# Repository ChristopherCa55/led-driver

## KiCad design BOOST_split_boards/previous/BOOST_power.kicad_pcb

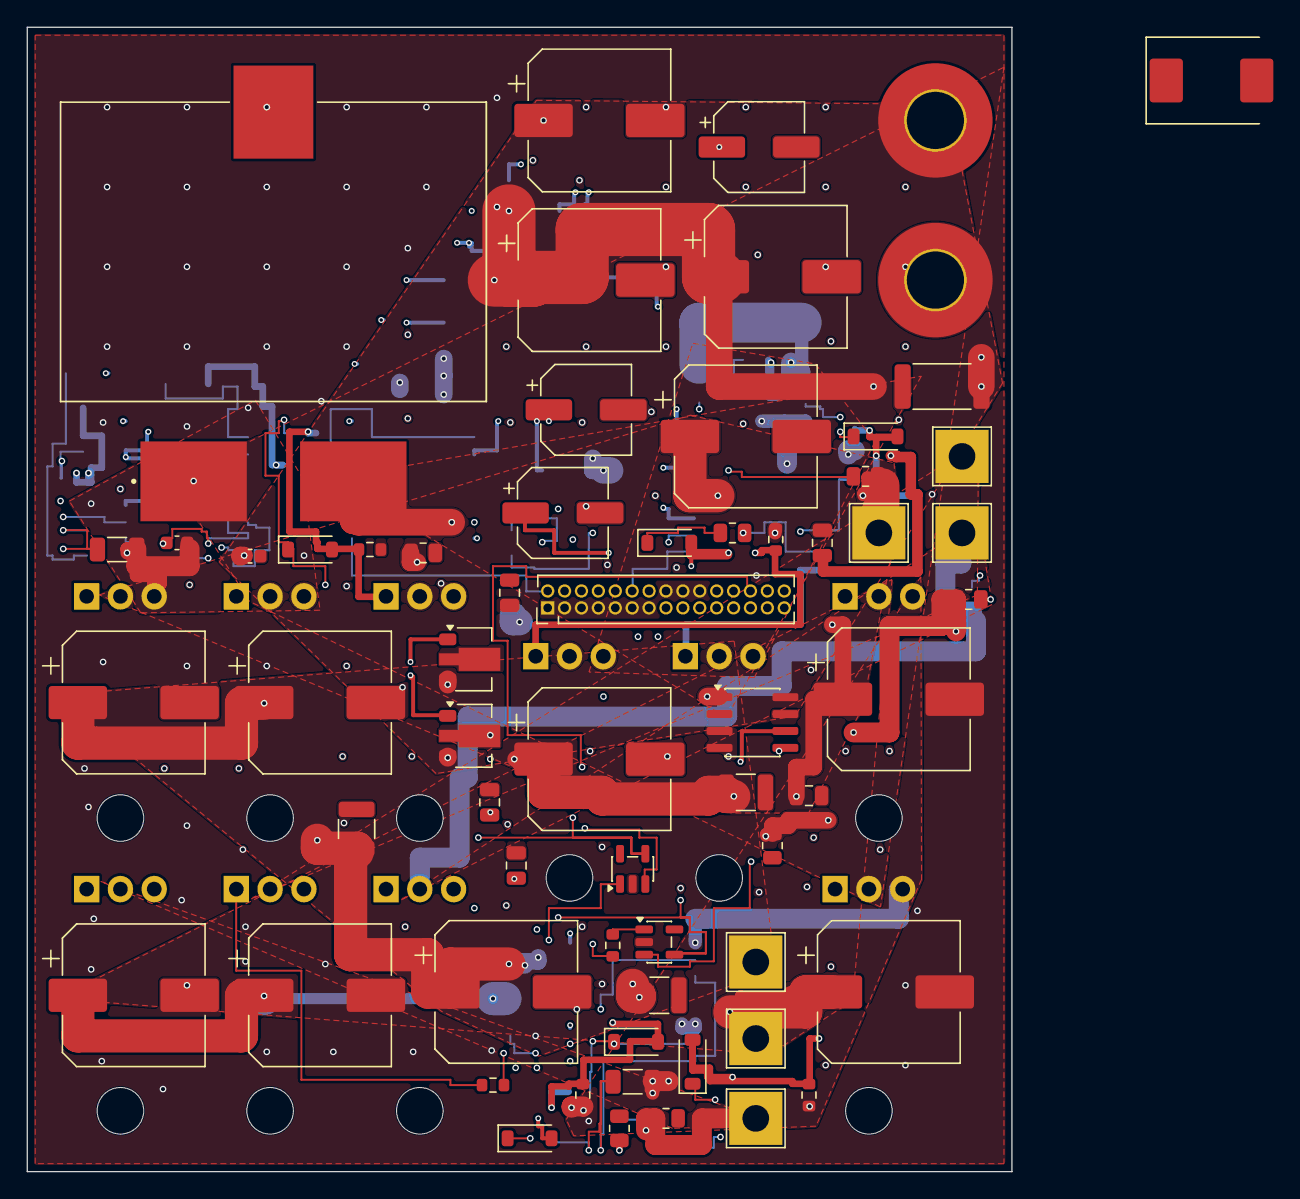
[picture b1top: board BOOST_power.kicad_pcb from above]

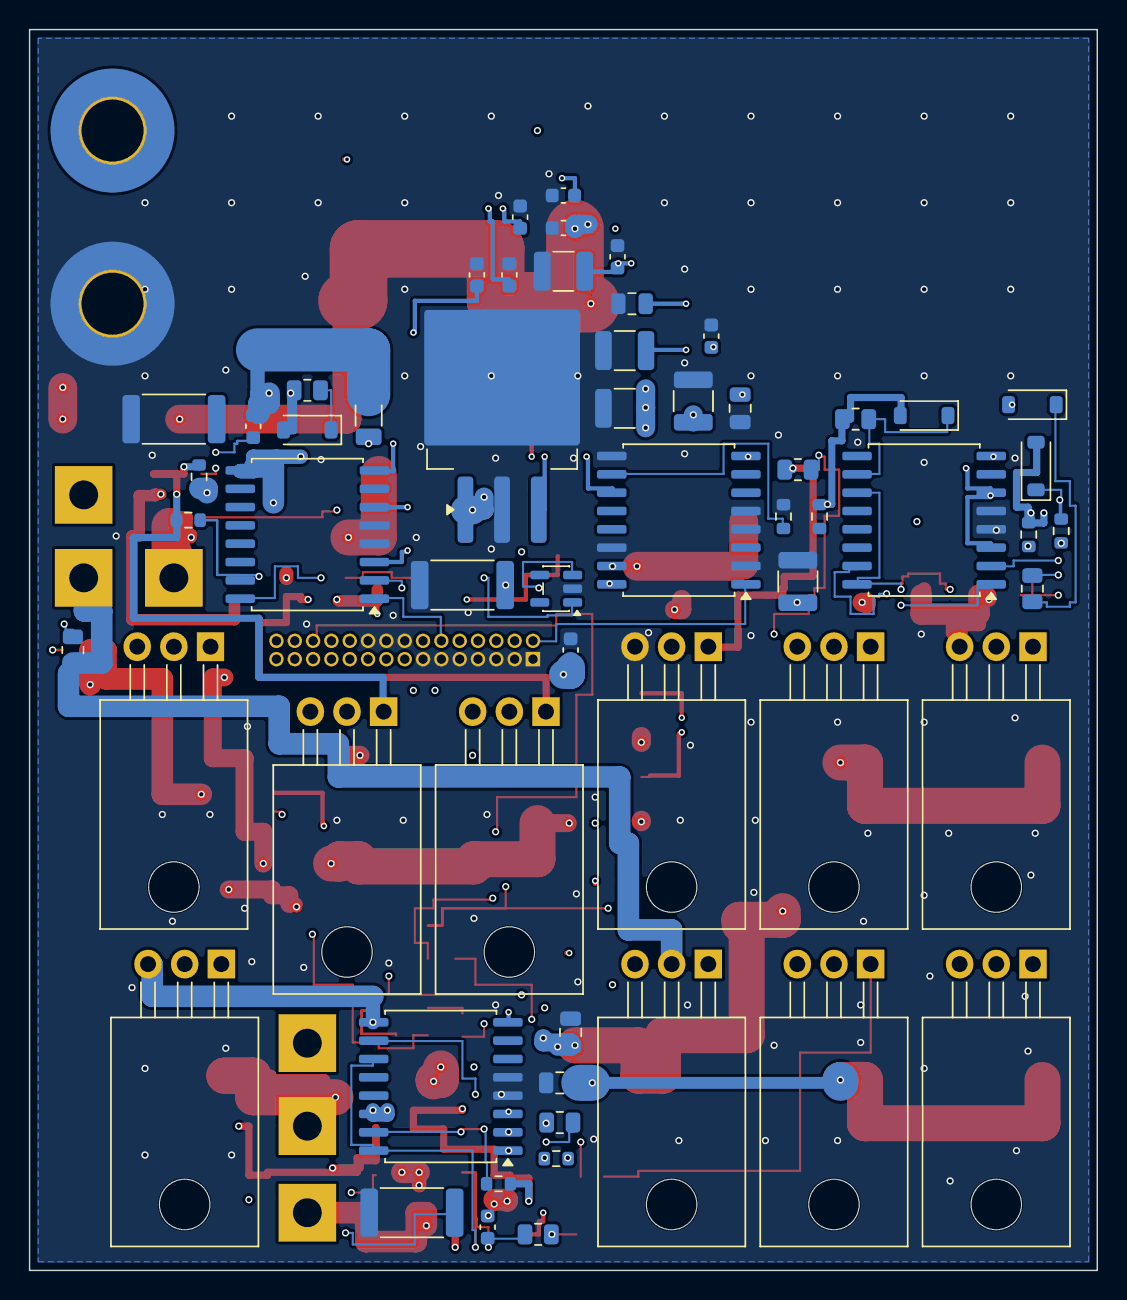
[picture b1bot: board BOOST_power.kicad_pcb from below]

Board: 8 copper layers, 74.0 x 86.0 mm, 121 parts (58 on the bottom side), 63 nets.

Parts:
C1, C4, C73: 4.7µ; C_1210_3225Metric
C3, C72, C76: 100n; C_0805_2012Metric
C6, C21, C25, C31, C62, C89: 1µ; C_0805_2012Metric
C7, C30, C55: 47µ; CP_Elec_6.3x5.4
C16, C18, C60: 2.2µ; C_1206_3216Metric
C20, C33, C34, C35, C48, C50, C51, C61, C82, C83, C84, C90: 100n; C_0603_1608Metric
C39, C56, C79, C80, C81: 10µ; C_1210_3225Metric
C40, C69, C85: 680µ; CP_Elec_10x12.5
C70, C71, C74, C75, C77, C78, C86, C87, C88: 220µ; CP_Elec_10x10.5
D2, D8, D9, D10, D11, D12, D13, D14, D21, D22: D; D_SOD-123
D19: TVS_5KP54A; D_SMC
J1, J2: Conn_01x01_Pin; MountingHole_4.3mm_M4_Pad_TopBottom
J3, J4, J5, J6, J7, J8: Conn_01x01_Pin; TestPoint_THTPad_4.0x4.0mm_Drill2.0mm
J10: Conn_2x15_1.27mm; PinHeader_2x15_P1.27mm_Vertical
L1: 6.8µ; IND_CSCF3218-6R8MC
M1, M2, M3, M4, M5, M6, M7, M8, M9, M10: HYG180N10; TO-220-3_Horizontal_TabDown
R1: 2m; R_2512_6332Metric
R7, R52, R53: .05; R_2512_6332Metric
R9, R35, R43: 18k; R_0805_2012Metric
R13, R22, R23, R47, R50, R56: 100; R_0603_1608Metric
R14: 1Meg; R_0805_2012Metric
R15, R59, R70: 5.1; R_0805_2012Metric
R21, R48, R60, R72: 5; R_0805_2012Metric
R25, R87, R94: 910k; R_0805_2012Metric
R49, R61, R62, R73, R74, R75, R76, R104: 10k; R_0603_1608Metric
U1, U17: L78L05_SOT89; SOT-89-3
U6, U11, U12: MCP6241; SOT-23-5
U8, U10, U15, U19: UCC21520DW; SOIC-16W_7.5x10.3mm_P1.27mm
U16: LM2940_12; TO-263-3_TabPin2
U25: INA241A3xD; SOIC-8_3.9x4.9mm_P1.27mm

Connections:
5V: C7.1, C39.1, C48.1, C62.2, C89.2, C90.1, J10.15, U8.3 (VCCI), U8.6 (DT), U8.8 (VCCI), U10.3 (VCCI), U10.6 (DT), U10.8 (VCCI), U15.3 (VCCI), U15.6 (DT), U15.8 (VCCI), U17.1 (OUT), U19.3 (VCCI), U19.6 (DT), U19.8 (VCCI)
12V: C6.1, C25.1, C30.1, C31.1, D9.2 (+), D10.2 (+), D21.2 (+), J10.19, U16.3 (OUT), U19.11 (VDDB), U19.16 (VDDA)
.1Vout_1: J10.22, R9.1
.1Vout_2: J10.23, R35.1
.1Vout_3: J10.24, R43.1
Current: J10.21, U25.5
GATE_M1: D12.2 (+), M1.1 (G), R15.2, R104.1
GATE_M2: D11.2 (+), M2.1 (G), R13.1, R75.2
GATE_M3: D14.2 (+), M3.1 (G), R23.2, R61.2
GATE_M4: D13.2 (+), M4.1 (G), R47.1, R73.2
GATE_M5: D22.2 (+), M5.1 (G), R59.1, R74.2
GATE_M6: D8.2 (+), M6.1 (G), R49.1, R70.2
GATE_M7: D2.2 (+), M7.1 (G), R60.2, R76.2
GND: C1.2, C3.2, C4.2, C6.2, C7.2, C20.2, C21.2, C25.2, C30.2, C31.2, C33.2, C34.2, C35.2, C39.2, C40.2, C48.2, C55.2, C56.2, C62.1, C69.2, C70.2, C71.2, C72.2, C73.2, C74.2, C75.2, C76.2, C77.2, C78.2, C79.2, C80.2, C81.2, C82.2, C83.2, C84.2, C85.2, C86.2, C87.2, C88.2, C89.1, C90.2, D19.2 (+), J2.1 (Pin_1_1), J10.1, J10.3, J10.5, J10.7, J10.9, J10.11, J10.13, J10.16, J10.18, J10.20, M1.3 (S), R7.2, R14.2, R52.2, R53.2, R62.2, R104.2, U1.2 (GND), U6.2 (V-), U8.4 (GND), U8.5 (DIS), U10.4 (GND), U10.5 (DIS), U11.2 (V-), U12.2 (V-), U15.4 (GND), U15.5 (DIS), U16.2 (GND), U17.2 (GND), U19.2 (INB), U19.4 (GND), U19.5 (DIS), U19.9 (VSSB), U19.14 (VSSA), U25.2 (GND), U25.3 (REF2), U25.4 (GND), U25.7 (REF1)
IREF1_input: J10.25, U11.3 (In+)
IREF2_input: J10.26, U12.3 (In+)
IREF3_input: J10.27, U6.3 (In+)
LX: D19.1 (-), L1.1, M1.2 (D), M5.2 (D), M6.2 (D), M7.2 (D), R14.1
M1_ON: J10.2, U19.1 (INA)
M2_ON: J10.4, U15.1 (INA)
unnamed: D2.1 (-), R60.1, U15.10 (OUTB)
unnamed: D8.1 (-), R70.1, U10.10 (OUTB)
unnamed: D9.1 (-), R48.1
unnamed: D10.1 (-), R21.1
unnamed: D11.1 (-), R13.2, U15.15 (OUTA)
unnamed: D12.1 (-), R15.1, U19.15 (OUTA)
unnamed: D13.1 (-), R47.2, U8.15 (OUTA)
unnamed: D14.1 (-), R23.1, U10.15 (OUTA)
unnamed: D21.1 (-), R72.1
unnamed: D22.1 (-), R59.2, U8.10 (OUTB)
unnamed: M8.1 (G), R22.1
unnamed: M8.3 (S), R7.1, U6.4 (In-)
unnamed: M9.1 (G), R50.1
unnamed: M9.3 (S), R53.1, U12.4 (In-)
unnamed: M10.1 (G), R56.1
unnamed: M10.3 (S), R52.1, U11.4 (In-)
unnamed: R22.2, U6.1 (OUT)
unnamed: C60.1, C61.1, R72.2, U8.11 (VDDB), U8.16 (VDDA)
unnamed: C16.1, C50.1, R48.2, U10.11 (VDDB), U10.16 (VDDA)
unnamed: R56.2, U11.1 (OUT)
unnamed: R50.2, U12.1 (OUT)
unnamed: C18.1, C51.1, R21.2, U15.11 (VDDB), U15.16 (VDDA)
unnamed: R62.1, U19.10 (OUTB)
unnamed: J10.28, R87.2
unnamed: J10.29, R25.2
unnamed: J10.30, R94.2
Output1_drain: J4.1 (Pin_1_1), M10.2 (D), R94.1
Output2_drain: J7.1 (Pin_1_1), M9.2 (D), R25.1
Output3_drain: J6.1 (Pin_1_1), M8.2 (D), R87.1
Vin: C40.1, C69.1, C79.1, C80.1, C81.1, C82.1, C83.1, C84.1, C85.1, J1.1 (Pin_1_1), R1.2, U1.3 (IN), U16.1 (IN), U17.3 (IN), U25.8 (+)
Vout_1: C1.1, C70.1, C72.1, C86.1, C88.1, J3.1 (Pin_1_1), M2.2 (D), R9.2
Vout_2: C3.1, C71.1, C73.1, C78.1, C87.1, J8.1 (Pin_1_1), M3.2 (D), R35.2
Vout_3: C4.1, C74.1, C75.1, C76.1, C77.1, J5.1 (Pin_1_1), M4.2 (D), R43.2
analog_5V: C20.1, C21.1, C33.1, C34.1, C35.1, C55.1, C56.1, J10.17, U1.1 (OUT), U6.5 (V+), U11.5 (V+), U12.5 (V+), U25.6 (V+)
ena_out_1: J10.6, U15.2 (INB)
ena_out_2: J10.8, U10.2 (INB)
ena_out_3: J10.10, U8.2 (INB)
m2_source: C18.2, C51.2, M2.3 (S), M7.3 (S), R75.1, R76.1, U15.9 (VSSB), U15.14 (VSSA)
m3_source: C16.2, C50.2, M3.3 (S), M6.3 (S), R49.2, R61.1, U10.9 (VSSB), U10.14 (VSSA)
m4_source: C60.2, C61.2, M4.3 (S), M5.3 (S), R73.1, R74.1, U8.9 (VSSB), U8.14 (VSSA)
out_2_on: J10.12, U10.1 (INA)
out_3_on: J10.14, U8.1 (INA)
rsense_lo: L1.2, R1.1, U25.1 (-)

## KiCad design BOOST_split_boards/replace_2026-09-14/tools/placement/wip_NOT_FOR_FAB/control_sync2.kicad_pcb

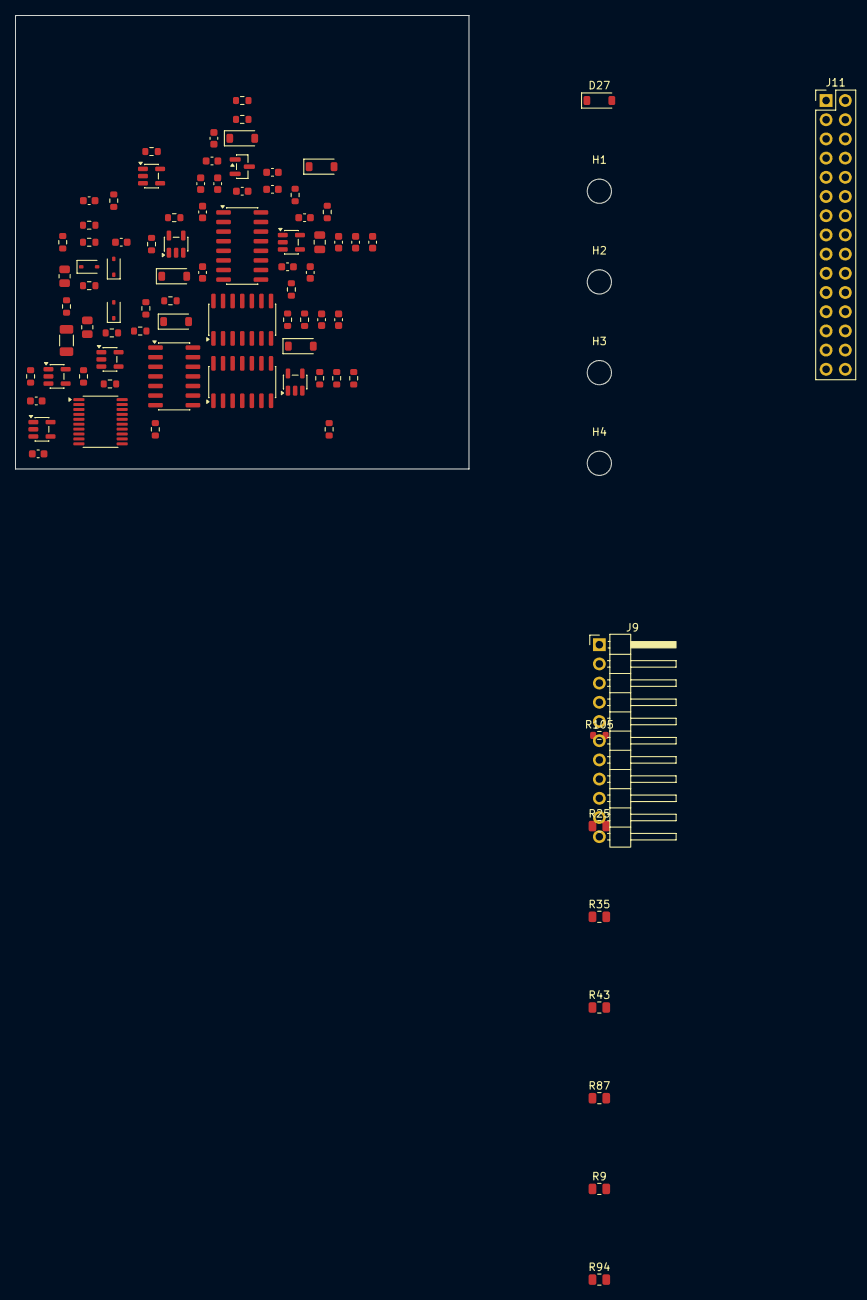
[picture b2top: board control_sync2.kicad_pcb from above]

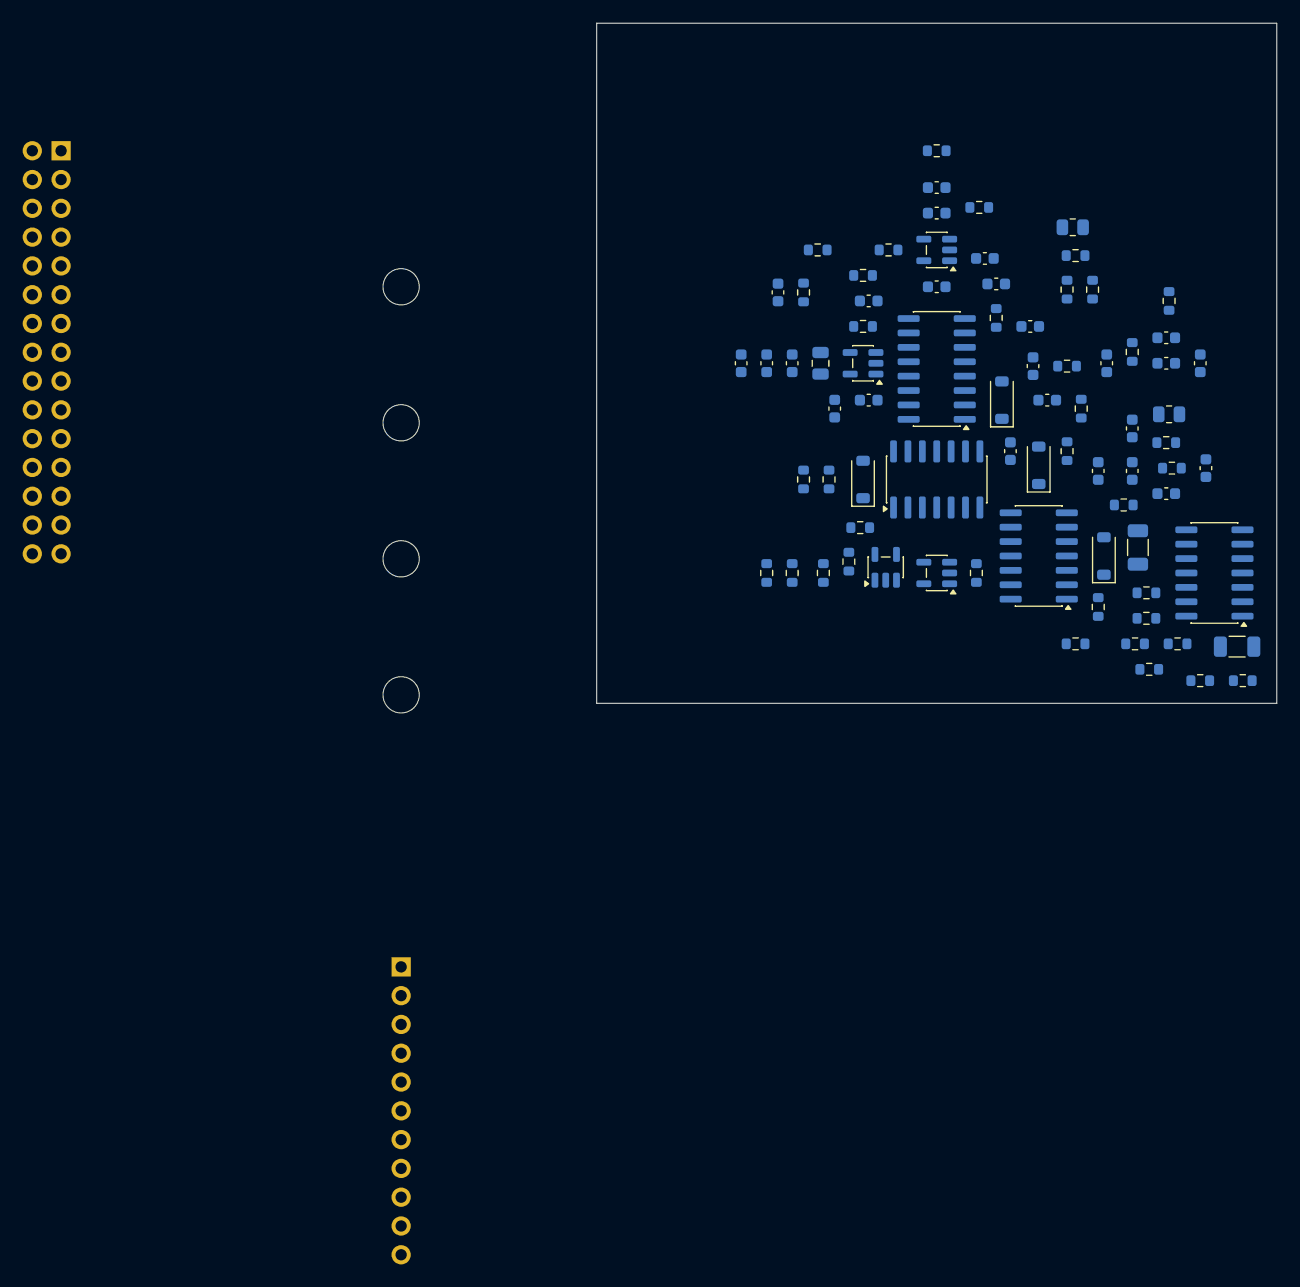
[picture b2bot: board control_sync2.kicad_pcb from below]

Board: 8 copper layers, 60.0 x 60.0 mm, 166 parts (78 on the bottom side), 105 nets, no tracks yet.

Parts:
C8, C9, C17, C19: 330p; C_0603_1608Metric
C10, C11, C13: 4.7n; C_0603_1608Metric
C12, C22, C23, C24, C26, C28, C29, C32, C36, C37, C38, C42, C43, C46, C52, C53, C54, C58, C59, C63, C65, C66, C68, C92, C94, C95, C96, C97, C98, C99, C104: 100n; C_0603_1608Metric
C14: 220p; C_0603_1608Metric
C15: 100p; C_0603_1608Metric
C47, C93, C103: 10u; C_0603_1608Metric
C49, C64, C67: 100n; C_1206_3216Metric
C57, C91: 1µ; C_0805_2012Metric
C100, C101, C102: 1n; C_0603_1608Metric
D1, D3, D4, D5, D6, D7, D15, D20, D24, D27: D; D_SOD-123
D23, D25, D26: D; D_SOD-323
H1, H2, H3, H4: MountingHole_M3; MountingHole_3.2mm_M3
J9: Conn_01x11; PinHeader_1x11_P2.54mm_Horizontal
J11: Conn_02x15_2.54mm; PinHeader_2x15_P2.54mm_Vertical
Q1: PNP; SOT-23
R2, R6, R31, R33, R39, R41, R67, R77, R83, R85, R99, R100, R101, R102, R103: 10k; R_0603_1608Metric
R3, R32, R40: 620k; R_0603_1608Metric
R4, R54, R55, R58, R71: 1k; R_0603_1608Metric
R8, R34, R42, R51, R63, R78, R80: 2k; R_0603_1608Metric
R9, R35, R43: 18k; R_0805_2012Metric
R11, R17: 510k; R_0603_1608Metric
R16, R19: 5.1k; R_0603_1608Metric
R18, R20: 200k; R_0603_1608Metric
R25, R87, R94: 910k; R_0805_2012Metric
R26, R64, R79, R81: 220; R_0603_1608Metric
R27, R37, R45: 4.7k; R_0603_1608Metric
R28, R36, R38, R44, R46, R88, R91, R95, R96, R105: 100k; R_0603_1608Metric
R29, R30, R57: 22k; R_0805_2012Metric
R65: 22k; R_0603_1608Metric
R66, R89, R92, R97: 3.3k; R_0603_1608Metric
R68: 62k; R_0603_1608Metric
R69: 20k; R_0603_1608Metric
R82: 56k; R_0603_1608Metric
R84: 120k; R_0603_1608Metric
R86: 1Meg; R_0805_2012Metric
R90, R93, R98: 10Meg; R_0603_1608Metric
U2, U4, U5, U14, U21: MCP6561; SOT-23-5
U3, U7, U13, U22, U23, U24: MCP6241; SOT-23-5
U18: 4017; SOIC-16_3.9x9.9mm_P1.27mm
U26: MCP4451-xxxx-ST; TSSOP-20_4.4x6.5mm_P0.65mm
U28: 74HC4051; SOIC-16_3.9x9.9mm_P1.27mm
U101, U102, U103: 74HC00; SOIC-14_3.9x8.7mm_P1.27mm
U104, U105: 74HC14; SOIC-14_3.9x8.7mm_P1.27mm
U106: CD74HC4066; SOIC-14_3.9x8.7mm_P1.27mm

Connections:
0A_hi: R11.1, U2.1 (OUT), U101.2 (B)
0err_hi: D1.2 (+), D3.1 (-), R18.1, R66.1, U4.1 (OUT), U104.11 (A)
5V: C12.1, C22.1, C23.1, C24.1, C26.1, C28.1, C29.1, C52.1, C53.2, C54.1, C57.2, C58.1, C91.2, C92.1, C94.1, C95.1, C96.1, C97.1, C98.1, C99.1, C104.1, J9.9, J11.10, R17.2, R20.2, R69.2, R82.1, R103.1, U2.5 (V+), U4.5 (V+), U5.5 (V+), U14.5 (V+), U18.16 (VDD), U21.5 (V+), U26.17 (VDD), U28.16 (VCC), U101.14 (VCC), U102.14 (VCC), U103.14 (VCC), U104.14 (VCC), U105.14 (VCC), U106.14 (VDD)
12V: J11.19, R84.1
.1Vout_1: R2.2, R8.1, R9.1
.1Vout_2: R31.2, R34.1, R35.1
.1Vout_3: R39.2, R42.1, R43.1
.1Vref_1: C46.1, D26.1 (-), R6.2, U3.3 (In+)
.1Vref_2: C43.1, D25.1 (-), R33.2, U7.3 (In+)
.1Vref_3: C42.1, D23.1 (-), R41.2, U13.3 (In+)
ARD_M1_INHIBIT: D27.2, J9.11, R105.1
Current: J11.23, U2.4 (In-), U5.3 (In+)
GND: C8.1, C9.1, C10.1, C11.1, C12.2, C13.1, C14.2, C15.2, C17.1, C19.2, C22.2, C23.2, C24.2, C26.2, C28.2, C29.2, C32.2, C36.1, C37.1, C38.1, C42.2, C43.2, C46.2, C47.2, C52.2, C53.1, C54.2, C57.1, C58.2, C59.2, C63.2, C65.2, C66.2, C68.2, C91.1, C92.2, C93.2, C94.2, C95.2, C96.2, C97.2, C98.2, C99.2, C100.2, C101.2, C102.2, C103.2, C104.2, J9.10, J11.1, J11.2, J11.11, J11.12, J11.20, J11.21, J11.24, J11.25, J11.28, J11.29, Q1.3 (C), R8.2, R16.2, R19.2, R28.1, R34.2, R36.2, R38.1, R42.2, R46.1, R54.2, R55.2, R58.2, R68.2, R83.2, R85.2, R88.2, R89.2, R92.2, R95.2, R97.2, R99.2, R102.2, R105.2, U2.2 (V-), U3.2 (V-), U4.2 (V-), U5.2 (V-), U7.2 (V-), U13.2 (V-), U14.2 (V-), U18.8 (VSS), U21.2 (V-), U22.2 (V-), U23.2 (V-), U24.2 (V-), U26.7 (VSS), U26.10 (P1A), U26.11 (P0A), U26.20 (P2A), U28.2 (A6), U28.4 (A7), U28.5 (A5), U28.6 (~E), U28.7 (VEE), U28.8 (GND), U28.12 (A3), U28.13 (A0), U101.7 (GND), U102.7 (GND), U103.7 (GND), U104.7 (GND), U105.7 (GND), U106.7 (VSS)
IREF1: J9.4, R29.1, U106.6 (CTRL)
IREF1_input: J11.26, U26.12 (P0W)
IREF2: J9.5, R30.1, U106.5 (CTRL)
IREF2_input: J11.27, U26.9 (P1W)
IREF3: J9.6, R57.1, U106.13 (CTRL)
IREF3_input: J11.30, U26.19 (P2W)
M1_INHIBIT: D1.1 (-), D15.1 (-), D24.1 (-), D27.1, R26.1, U104.1 (A)
M1_ON: J11.3, U101.5 (B), U104.2 (Y)
M2_ON: J11.4, U104.4 (Y)
unnamed: C8.2, R63.1, R64.1
unnamed: C9.2, R78.1, R79.1
unnamed: C17.2, R80.1, R81.1
unnamed: C19.1, R26.2, R51.2
unnamed: D3.2 (+), R65.2
unnamed: D4.2 (+), Q1.1 (B), R65.1
unnamed: C15.1, D4.1 (-), R71.1
unnamed: D5.2 (+), R63.2, U103.3 (Y)
unnamed: D5.1 (-), R64.2, U105.3 (A)
unnamed: D7.2 (+), R78.2, U102.8 (Y)
unnamed: D7.1 (-), R79.2, U104.13 (A)
unnamed: D20.2 (+), R80.2, U102.6 (Y)
unnamed: D20.1 (-), R81.2, U105.1 (A)
unnamed: C49.2, D23.2 (+), R90.2, U22.1 (OUT)
unnamed: D24.2 (+), R86.1, U21.1 (OUT)
unnamed: C64.2, D25.2 (+), R93.2, U23.1 (OUT)
unnamed: C67.2, D26.2 (+), R98.2, U24.1 (OUT)
unnamed: C14.1, Q1.2 (E), R66.2, U14.4 (In-)
unnamed: R11.2, R16.1, R17.1, U2.3 (In+)
unnamed: R2.1, R3.2, U3.4 (In-)
unnamed: R18.2, R19.1, R20.1, U4.3 (In+)
unnamed: R31.1, R32.2, U7.4 (In-)
unnamed: R39.1, R40.2, U13.4 (In-)
unnamed: R67.2, R68.1, R69.1, U14.3 (In+)
unnamed: U18.7 (Q3), U18.15 (Reset)
unnamed: R82.2, R85.1, R86.2, U21.3 (In+)
unnamed: R83.1, R84.2, U21.4 (In-)
unnamed: C59.1, R44.2, R89.1, U22.3 (In+)
unnamed: C65.1, R91.2, R92.1, U23.3 (In+)
unnamed: C68.1, R96.2, R97.1, U24.3 (In+)
unnamed: C100.1, R29.2, R54.1, U26.13 (P0B)
unnamed: C101.1, R30.2, R55.1, U26.8 (P1B)
unnamed: C102.1, R57.2, R58.1, U26.18 (P2B)
unnamed: R99.1, U26.16 (A1)
unnamed: R102.1, U26.4 (HVC/A0)
unnamed: R103.2, U26.15 (~RESET)
unnamed: R4.2, U101.3 (Y)
unnamed: U102.3 (Y), U104.3 (A)
unnamed: U18.3 (Q0), U28.11 (S0), U102.4 (A)
unnamed: U18.2 (Q1), U28.10 (S1), U102.10 (A)
unnamed: U102.11 (Y), U104.5 (A)
unnamed: U18.4 (Q2), U28.9 (S2), U103.1 (A)
unnamed: U103.6 (Y), U104.9 (A)
unnamed: R87.2, R88.1, U106.1 (A)
unnamed: C49.1, R90.1, U22.4 (In-), U106.2 (B)
unnamed: R25.2, R36.1, U106.3 (A)
unnamed: C64.1, R93.1, U23.4 (In-), U106.4 (B)
unnamed: R94.2, R95.1, U106.8 (A)
unnamed: C67.1, R98.1, U24.4 (In-), U106.9 (B)
Out: U101.8 (Y), U101.13 (A)
Out-: D15.2 (+), R51.1, U18.13 (CKEN), U101.9 (B), U101.11 (Y), U102.1 (A), U102.13 (A), U103.5 (B)
Output1_drain: J11.14, R94.1
Output2_drain: J11.16, R25.1
Output3_drain: J11.18, R87.1
RESET-: U101.6 (Y), U101.12 (B)
Reset_raw: U5.1 (OUT), U101.4 (A)
SCL: J9.7, U26.5 (SCL)
SDA: J9.8, U26.6 (SDA)
V_err: U4.4 (In-), U5.4 (In-), U28.3 (A)
Verr1: C13.2, R27.2, R28.2, U28.14 (A1)
Verr2: C11.2, R37.2, R38.2, U28.15 (A2)
Verr3: C10.2, R45.2, R46.2, U28.1 (A4)
VerrGT0: U101.1 (A), U102.5 (B), U102.9 (B), U103.2 (B), U104.10 (Y)
Voltage_err_1: R3.1, R27.1, U3.1 (OUT)
Voltage_err_2: R32.1, R37.1, U7.1 (OUT)
Voltage_err_3: R40.1, R45.1, U13.1 (OUT)
Vout_1: J11.13, R9.2
Vout_2: J11.15, R35.2
Vout_3: J11.17, R43.2
Vref_1: C103.1, R6.1, R101.2
Vref_1_arduino: J9.1, R101.1
Vref_2: C93.1, R33.1, R100.2
Vref_2_arduino: J9.2, R100.1
Vref_3: C47.1, R41.1, R77.2
Vref_3_arduino: J9.3, R77.1
analog_5V: C32.1, C36.2, C37.2, C38.2, C63.1, C66.1, J11.22, R44.1, R91.1, R96.1, U3.5 (V+), U7.5 (V+), U13.5 (V+), U22.5 (V+), U23.5 (V+), U24.5 (V+)
ena_out_1: J11.5, U102.2 (B), U105.2 (Y)
ena_out_2: J11.7, U102.12 (B), U104.12 (Y)
ena_out_3: J11.9, U103.4 (A), U105.4 (Y)
low_error_timeout: D6.1 (-), R67.1, R71.2, U14.1 (OUT), U18.14 (CLK)
out_2_on: J11.6, U104.6 (Y)
out_3_on: J11.8, U104.8 (Y)
set-: D6.2 (+), R4.1, U101.10 (A)
